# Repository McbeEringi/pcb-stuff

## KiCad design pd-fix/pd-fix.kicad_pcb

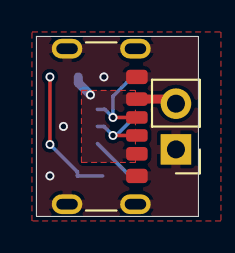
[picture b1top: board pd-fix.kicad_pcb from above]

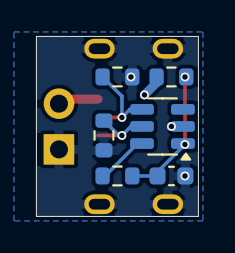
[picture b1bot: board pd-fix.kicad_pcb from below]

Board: 2 copper layers, 9.0 x 10.0 mm, 8 parts (6 on the bottom side), 6 nets.

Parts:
C1: 1u; C_0603_1608Metric
J1: USB_C_Receptacle_PowerOnly_6P; USB_C_Receptacle_GCT_USB4125-xx-x_6P_TopMnt_Horizontal
J2: Conn_01x02_Pin; PinHeader_1x02_P2.54mm_Vertical
R1: 1k; R_0603_1608Metric
R2, R3: 4.7k; R_0603_1608Metric
R4: R; R_0603_1608Metric
U1: CH221K; SOT-23-6

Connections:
CC1: J1.A5 (CC1), R2.1, U1.4 (CC1)
CC2: J1.B5 (CC2), R3.1, U1.5 (CC2)
GND: C1.2, J1.A12 (GND), J1.B12 (GND), J1.S1 (SHIELD), J2.1, R2.2, R3.2, U1.2 (GND)
unnamed: R4.2, U1.6 (CFG)
VBUS: J1.A9 (VBUS), J1.B9 (VBUS), J2.2, R1.1
VDD: C1.1, R1.2, R4.1, U1.1 (VDD)
